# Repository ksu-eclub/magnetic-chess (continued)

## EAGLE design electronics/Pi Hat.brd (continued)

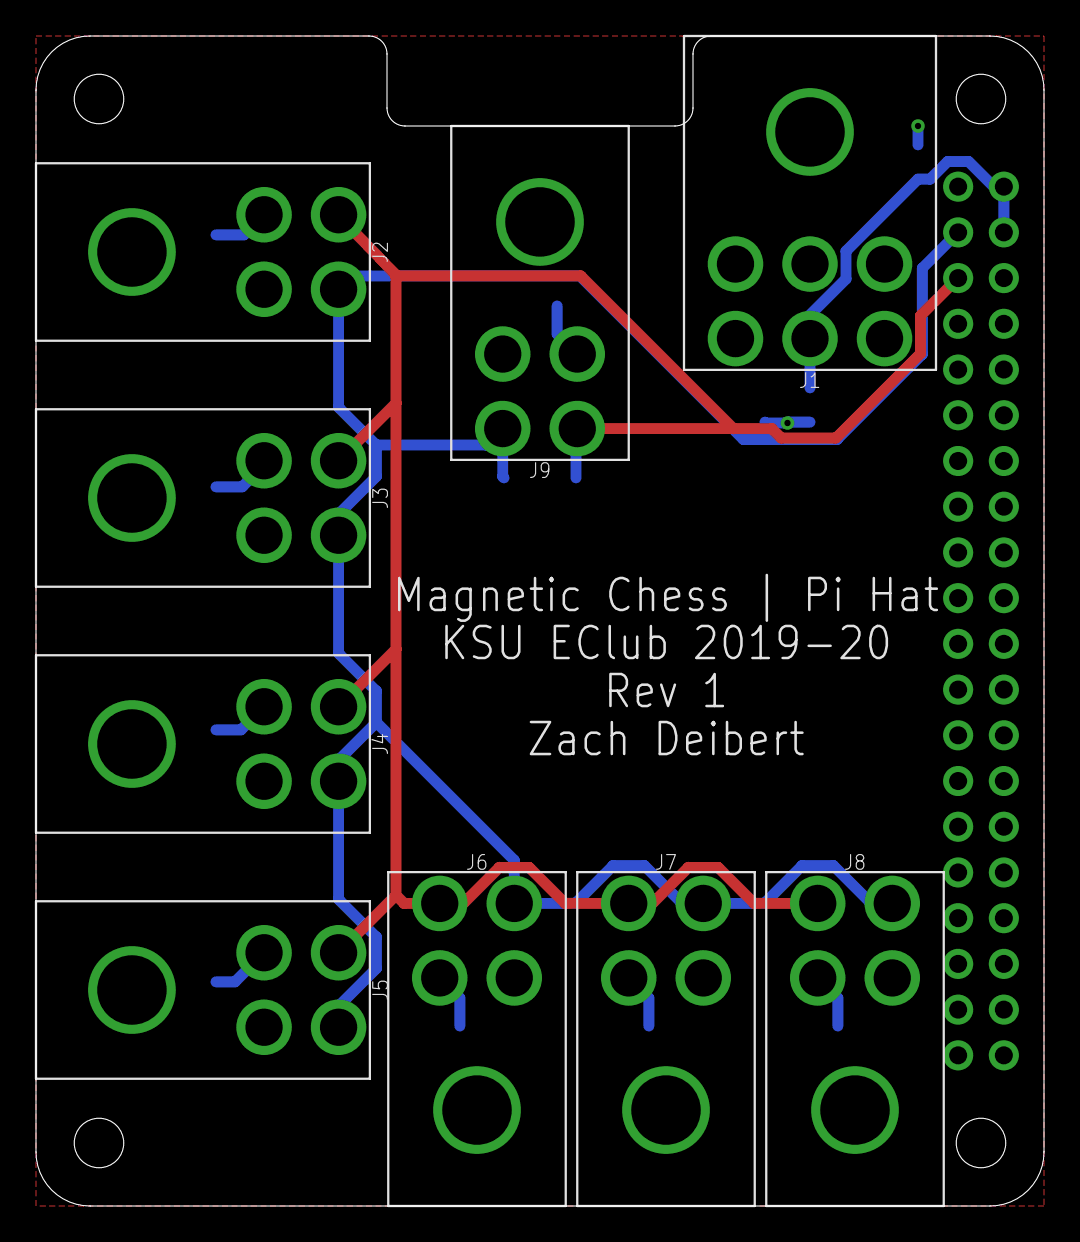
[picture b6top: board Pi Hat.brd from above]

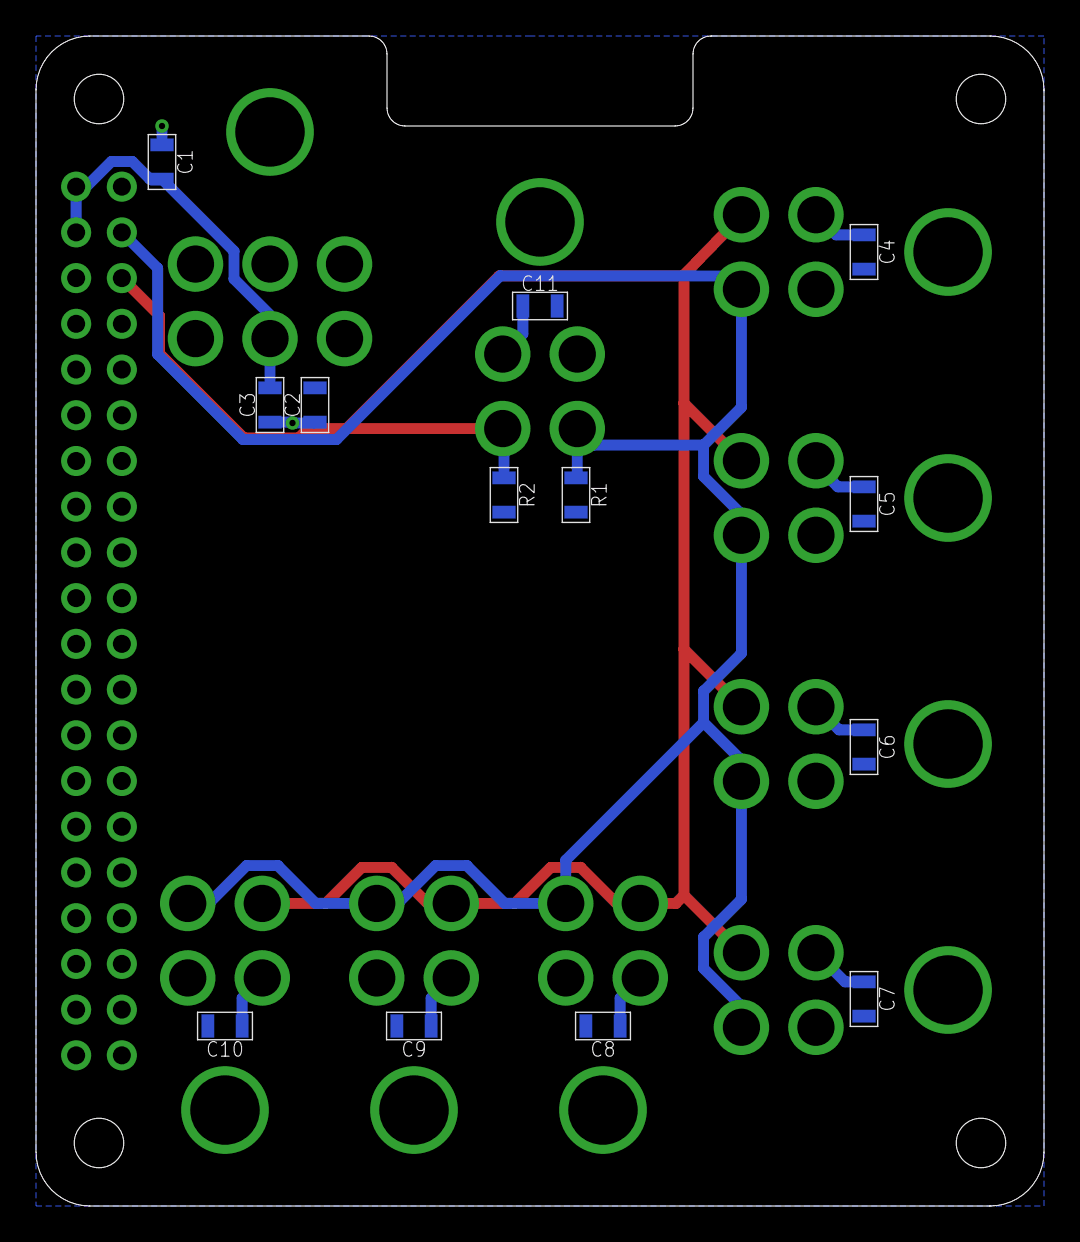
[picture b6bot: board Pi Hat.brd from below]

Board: 2 copper layers, 56.0 x 65.0 mm, 23 parts (13 on the bottom side), 6 nets.

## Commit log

2019-12-11 Created project
2019-12-11 I made a relay, Digi Pot, and BJT
2019-12-11 made symbols for rectifier, diode, and n-channel MOSFET
2019-12-11 Copied some parts over
2019-12-11 Created .gitignore
2019-12-13 added Miranda.lbr; added stepper part
2020-01-01 Added power symbols
2020-01-01 started stepper schematic
2020-01-02 Added some more components
2020-01-02 Added ATMEGA328PB
2020-01-03 Created connector parts
2020-01-27 Imported stepper driver from other project
2020-01-28 Added crystal
2020-01-28 Everything on the stepper driver schematic except the JST connectors for the motors
2020-01-28 Added electromagnet
2020-01-29 Added some connectors
2020-02-11 Added some components
2020-02-11 Stepper schematic is done. Ready for checkover
2020-02-11 Fixed capacitor mapping
2020-02-11 Added relay
2020-02-11 power entry started
2020-02-11 Routing crap
2020-02-11 Added MCU
2020-02-11 Ignored eagle.epf
2020-02-11 Created Pi hat board
2020-02-11 Created LED module board
2020-02-12 Finished stepper layout.
2020-02-12 Created LED controller PCB
2020-02-12 Made board ID consistent
2020-02-12 Added board ID
2020-02-12 Finished magnet driver schematic
2020-02-12 Added current-limiting resistors for LEDs
2020-02-12 Added pull-up on RESET
2020-02-13 finished stepper
2020-02-13 Fixed some problems with the magnet driver board
2020-02-13 Added mounting holes
2020-02-17 Initial check-in of SolidWorks files
2020-02-17 Added PCB models
2020-02-17 Added chess board models
2020-02-17 Added pieces
2020-02-17 Added standoffs and touch screen
2020-02-17 Made box
2020-02-17 Added power supply
2020-02-17 Added other commercial parts
2020-02-19 Modeled lots of it in SolidWorks
2020-02-19 More updates to box design
2020-02-19 Finished up SolidWorks model
2020-02-19 Wrote skeletons for hardware drivers
2020-02-19 Created UI skeleton
2020-02-20 Added protocol definition
2020-02-20 Ignored SolidWorks temp files
2020-02-20 Made all the wood MDF
2020-02-20 Added dovetails
2020-02-20 Added laser-cutting file
2020-02-20 Added logic skeleton
2020-02-21 Wrote code to generate RPC code into UI
2020-02-21 Created skeleton RPC methods
2020-02-21 Cleaned up stepper driver
2020-02-21 Created laser-cutting files
2020-02-23 Created 3D printing files
2020-02-26 Fixed some problems with the printed parts
2020-02-28 Designed pulley spacer
2020-02-28 Implemented starting the RPC service
2020-02-28 Implemented basic RPC client methods
2020-02-28 Added envoy Docker image for testing
2020-02-29 Found a better proxying solution
2020-03-01 Implemented streaming API
2020-03-01 Proxied ChessServiceImpl methods into logic.c methods
2020-03-01 Proxied rpc methods into magnetic-chess.js methods
2020-03-01 Added selection listener
2020-03-01 Implemented streaming through logic.c
2020-03-01 Added console for testing logic without RPC code
2020-03-01 Added skeleton for hardware interfacing code
2020-03-06 Created jig for soldering LED modules together
2020-03-06 Created voice control project
2020-03-06 Wrote test code for voice recognition
2020-03-06 Removed unneeded files
2020-03-06 Fixed null problem
2020-03-08 Wrote initial version of BLE server
2020-03-09 Wrote bluetooth connection code for app
2020-03-09 Made it connect to the GATT server
2020-03-09 First minimal working version of app
2020-03-09 Fixed argument
2020-03-09 Wrote documentation comment about the file
2020-03-09 Cleaned up the code
2020-03-09 Added progress bar to scanning activity
2020-03-09 Created logo for app
2020-03-09 Redid comments
2020-03-09 Implemented voice control server
2020-03-09 Fixed error handling
2020-03-09 Fixed compiling on Pi
2020-03-10 compiling logit-listener.c
2020-03-10 Fixed build script
2020-03-10 Worked on logic.c
    Finished board reset and added getmoves for rook
2020-03-11 started magnet.ino
2020-03-11 Update check
2020-03-11 Update logic.c
    Finished up the getMove function.
    Still need to check if the king is in check and not allow him to move into check. Also need to allow castling
2020-04-04 Bump acorn from 6.4.0 to 6.4.1 in /ui/rpc
    Bumps [acorn](https://github.com/acornjs/acorn) from 6.4.0 to 6.4.1.
    - [Release notes](https://github.com/acornjs/acorn/releases)
    - [Commits](https://github.com/acornjs/acorn/compare/6.4.0...6.4.1)
2020-04-05 Updated dependencies
2020-05-27 Updated plugin
2020-08-01 Bump elliptic from 6.5.2 to 6.5.3 in /ui/rpc
    Bumps [elliptic](https://github.com/indutny/elliptic) from 6.5.2 to 6.5.3.
    - [Release notes](https://github.com/indutny/elliptic/releases)
    - [Commits](https://github.com/indutny/elliptic/compare/v6.5.2...v6.5.3)
2020-09-12 Bump yargs-parser from 13.1.1 to 13.1.2 in /ui/rpc
    Bumps [yargs-parser](https://github.com/yargs/yargs-parser) from 13.1.1 to 13.1.2.
    - [Release notes](https://github.com/yargs/yargs-parser/releases)
    - [Changelog](https://github.com/yargs/yargs-parser/blob/master/docs/CHANGELOG-full.md)
    - [Commits](https://github.com/yargs/yargs-parser/commits)
2020-09-23 Restructured logic project
2020-09-26 Added main file to CMakeLists
2020-09-28 Wrote mock UI
2020-10-07 Basic UI framework and chess piece movement added
    --Added chess piece movement, coordinate interpretation
    --Added basic UI framework and styling
    --Added image assets (these are from wikimedia, attribution will come later)
2020-10-07 Revert "Merge branch 'master' of https://github.com/ksu-eclub/magnetic-chess"
    This reverts commit ea173fd52c3bd7b0f124d74abdd83c6e1d2f66b7, reversing
    changes made to 6094d07b73f3d3bad6c6a041d6815f238d70e16d.
2020-10-14 Fixed ea173fd..8944dce
2020-10-14 Incorporated old RPC code into logic build
2020-12-12 Bump ini from 1.3.5 to 1.3.8 in /ui/rpc
    Bumps [ini](https://github.com/isaacs/ini) from 1.3.5 to 1.3.8.
    - [Release notes](https://github.com/isaacs/ini/releases)
    - [Commits](https://github.com/isaacs/ini/compare/v1.3.5...v1.3.8)
2020-12-30 Fixed API CORS proxy
2020-12-30 Fixed protoc paths
2021-01-14 nicholasgerhold@ksu.edu
    added a board converter function to change an 8 by 8 array into a 64 char array, also added onchange and onselect to the reset board and get moves functions respectively.
2021-03-10 Bump elliptic from 6.5.3 to 6.5.4 in /ui/rpc
    Bumps [elliptic](https://github.com/indutny/elliptic) from 6.5.3 to 6.5.4.
    - [Release notes](https://github.com/indutny/elliptic/releases)
    - [Commits](https://github.com/indutny/elliptic/compare/v6.5.3...v6.5.4)
2021-05-11 Bump lodash from 4.17.20 to 4.17.21 in /ui/rpc
    Bumps [lodash](https://github.com/lodash/lodash) from 4.17.20 to 4.17.21.
    - [Release notes](https://github.com/lodash/lodash/releases)
    - [Commits](https://github.com/lodash/lodash/compare/4.17.20...4.17.21)
2021-05-26 Bump browserslist from 4.16.0 to 4.16.6 in /ui/rpc
    Bumps [browserslist](https://github.com/browserslist/browserslist) from 4.16.0 to 4.16.6.
    - [Release notes](https://github.com/browserslist/browserslist/releases)
    - [Changelog](https://github.com/browserslist/browserslist/blob/main/CHANGELOG.md)
    - [Commits](https://github.com/browserslist/browserslist/compare/4.16.0...4.16.6)
2021-08-12 Bump path-parse from 1.0.6 to 1.0.7 in /ui/rpc
    Bumps [path-parse](https://github.com/jbgutierrez/path-parse) from 1.0.6 to 1.0.7.
    - [Release notes](https://github.com/jbgutierrez/path-parse/releases)
    - [Commits](https://github.com/jbgutierrez/path-parse/commits/v1.0.7)
    ---
    updated-dependencies:
    - dependency-name: path-parse
2022-01-27 Bump cached-path-relative from 1.0.2 to 1.1.0 in /ui/rpc
    Bumps [cached-path-relative](https://github.com/ashaffer/cached-path-relative) from 1.0.2 to 1.1.0.
    - [Release notes](https://github.com/ashaffer/cached-path-relative/releases)
    - [Commits](https://github.com/ashaffer/cached-path-relative/commits)
    ---
    updated-dependencies:
    - dependency-name: cached-path-relative
2022-03-26 Bump minimist from 1.2.5 to 1.2.6 in /ui/rpc
    Bumps [minimist](https://github.com/substack/minimist) from 1.2.5 to 1.2.6.
    - [Release notes](https://github.com/substack/minimist/releases)
    - [Commits](https://github.com/substack/minimist/compare/1.2.5...1.2.6)
    ---
    updated-dependencies:
    - dependency-name: minimist
2022-06-23 Bump shell-quote from 1.7.2 to 1.7.3 in /ui/rpc
    Bumps [shell-quote](https://github.com/substack/node-shell-quote) from 1.7.2 to 1.7.3.
    - [Release notes](https://github.com/substack/node-shell-quote/releases)
    - [Changelog](https://github.com/substack/node-shell-quote/blob/master/CHANGELOG.md)
    - [Commits](https://github.com/substack/node-shell-quote/compare/v1.7.2...1.7.3)
    ---
    updated-dependencies:
2022-07-20 Bump terser from 5.5.1 to 5.14.2 in /ui/rpc
    Bumps [terser](https://github.com/terser/terser) from 5.5.1 to 5.14.2.
    - [Release notes](https://github.com/terser/terser/releases)
    - [Changelog](https://github.com/terser/terser/blob/master/CHANGELOG.md)
    - [Commits](https://github.com/terser/terser/commits)
    ---
    updated-dependencies:
